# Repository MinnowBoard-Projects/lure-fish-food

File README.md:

# Fish Food Lure for MinnowBoard SBC.

**Fish Food Lure** is a breadboard adapter for the MinnowBoard MAX / Turbot single boards computers (because you feed bread to fish).   
This lure enables fast prototyping on a breadboard, connects to the MinnowBoard using a ribbon cable.      

Lure naming credit goes to John Hawley aka [Warthog9](https://github.com/warthog9) 

You can purchase this lure with *[Netgate](https://store.netgate.com/Lures/FishFood.aspx)*.

> Released under the Creative Commons Attribution 3.0 License     
> https://creativecommons.org/licenses/by/3.0/   
> Designed using DipTrace 3.0

## KiCad version added to this repository. 

> Released under the Creative Commons Attribution 3.0 License     
> https://creativecommons.org/licenses/by/3.0/   
> Designed using KiCad 4.0.7
> Located in this directory: Fish_Food_Lure_KiCad

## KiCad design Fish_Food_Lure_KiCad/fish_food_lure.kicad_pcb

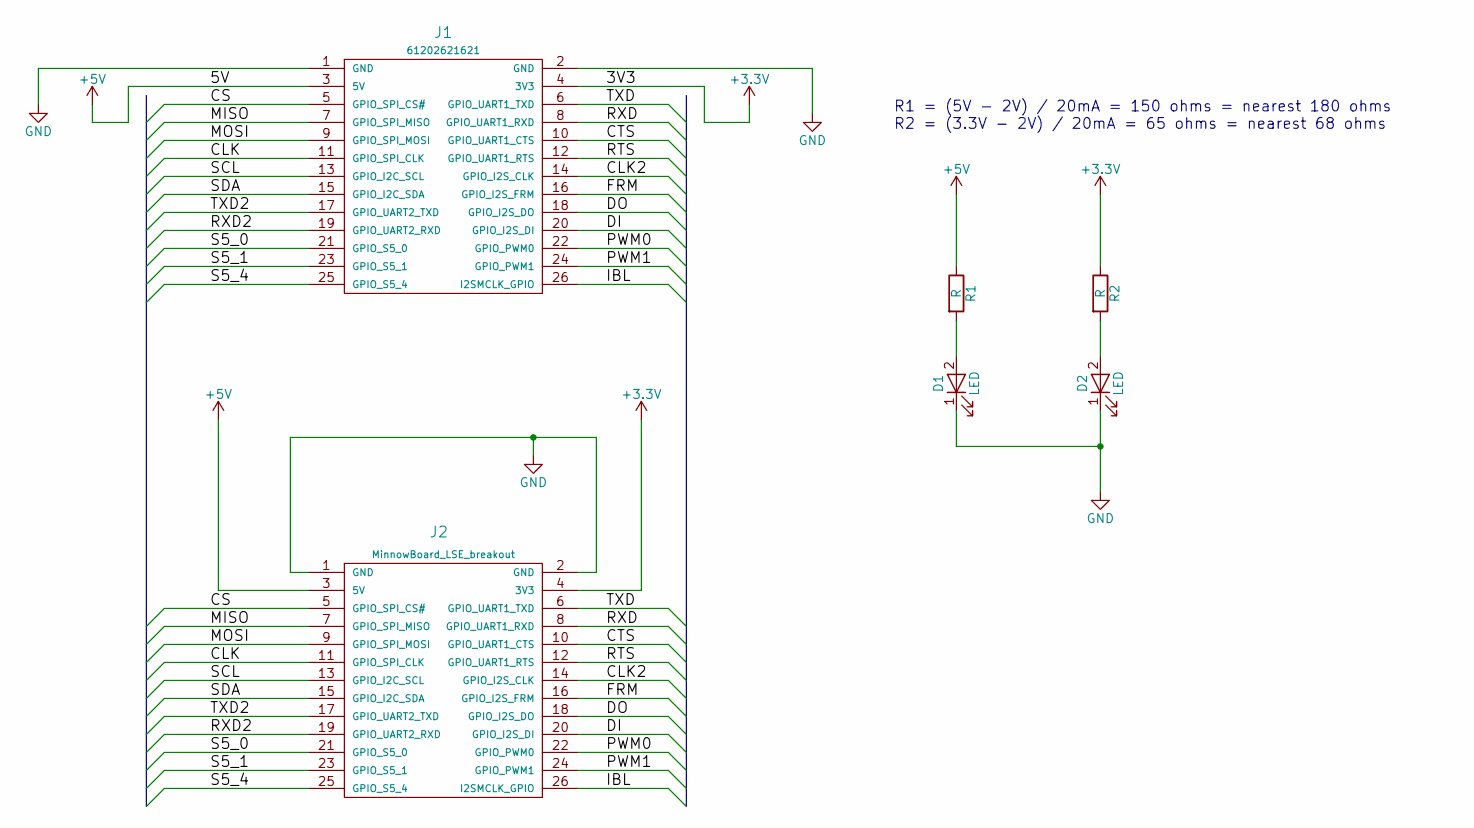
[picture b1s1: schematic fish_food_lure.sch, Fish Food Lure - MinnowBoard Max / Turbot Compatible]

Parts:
D1, D2: LED; LED_0805
J1: 61202621621
J2: MinnowBoard_LSE_breakout; 26_pin_breadboard
R1, R2: R; R_0805

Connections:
+3V3: J1.4 (3V3), J2.4 (3V3), R2.1
+5V: J1.3 (5V), J2.3 (5V), R1.1
/CLK: J1.11 (GPIO_SPI_CLK), J2.11 (GPIO_SPI_CLK)
/CLK2: J1.14 (GPIO_I2S_CLK), J2.14 (GPIO_I2S_CLK)
/CS: J1.5 (GPIO_SPI_CS#), J2.5 (GPIO_SPI_CS#)
/CTS: J1.10 (GPIO_UART1_CTS), J2.10 (GPIO_UART1_CTS)
/DI: J1.20 (GPIO_I2S_DI), J2.20 (GPIO_I2S_DI)
/DO: J1.18 (GPIO_I2S_DO), J2.18 (GPIO_I2S_DO)
/FRM: J1.16 (GPIO_I2S_FRM), J2.16 (GPIO_I2S_FRM)
/IBL: J1.26 (I2SMCLK_GPIO), J2.26 (I2SMCLK_GPIO)
/MISO: J1.7 (GPIO_SPI_MISO), J2.7 (GPIO_SPI_MISO)
/MOSI: J1.9 (GPIO_SPI_MOSI), J2.9 (GPIO_SPI_MOSI)
/PWM0: J1.22 (GPIO_PWM0), J2.22 (GPIO_PWM0)
/PWM1: J1.24 (GPIO_PWM1), J2.24 (GPIO_PWM1)
/RTS: J1.12 (GPIO_UART1_RTS), J2.12 (GPIO_UART1_RTS)
/RXD: J1.8 (GPIO_UART1_RXD), J2.8 (GPIO_UART1_RXD)
/RXD2: J1.19 (GPIO_UART2_RXD), J2.19 (GPIO_UART2_RXD)
/S5_0: J1.21 (GPIO_S5_0), J2.21 (GPIO_S5_0)
/S5_1: J1.23 (GPIO_S5_1), J2.23 (GPIO_S5_1)
/S5_4: J1.25 (GPIO_S5_4), J2.25 (GPIO_S5_4)
/SCL: J1.13 (GPIO_I2C_SCL), J2.13 (GPIO_I2C_SCL)
/SDA: J1.15 (GPIO_I2C_SDA), J2.15 (GPIO_I2C_SDA)
/TXD: J1.6 (GPIO_UART1_TXD), J2.6 (GPIO_UART1_TXD)
/TXD2: J1.17 (GPIO_UART2_TXD), J2.17 (GPIO_UART2_TXD)
GND: D1.1 (K), D2.1 (K), J1.1 (GND), J1.2 (GND), J2.1 (GND), J2.2 (GND)
unnamed: D1.2 (A), R1.2
unnamed: D2.2 (A), R2.2

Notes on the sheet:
R1 = (5V - 2V) / 20mA = 150 ohms = nearest 180 ohms R2 = (3.3V - 2V) / 20mA = 65 ohms = nearest 68 ohms

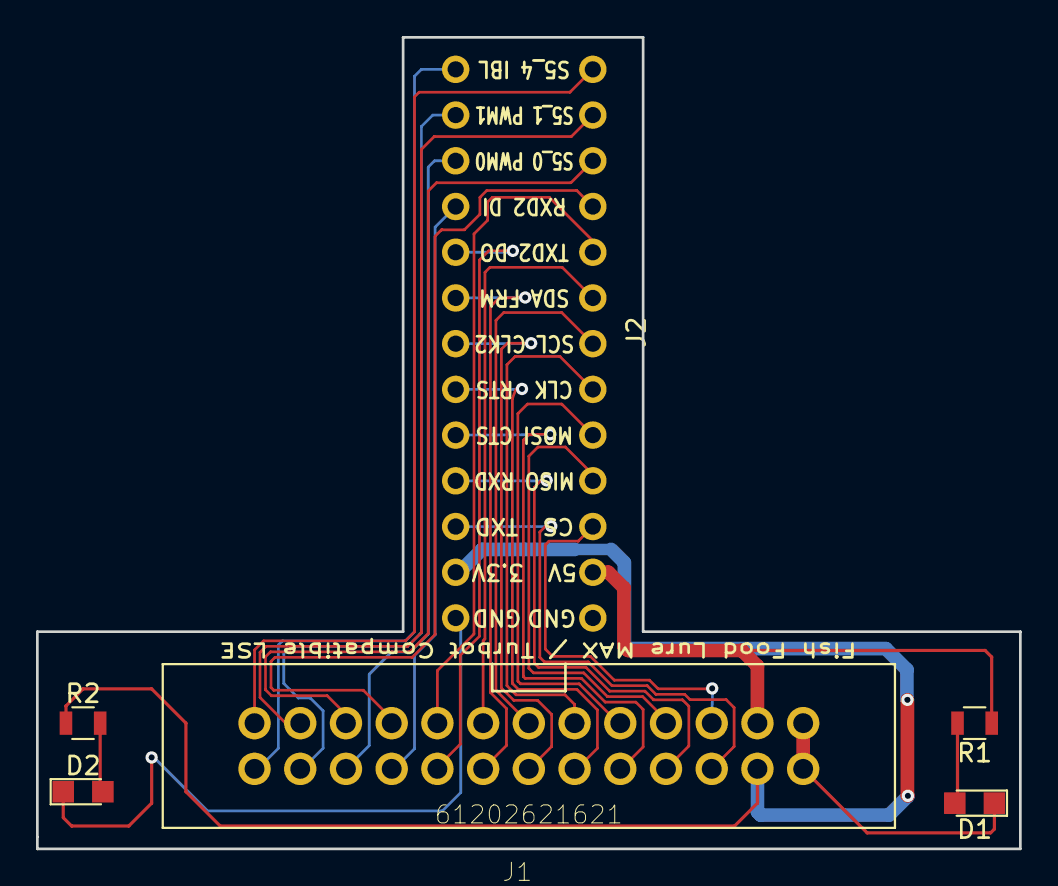
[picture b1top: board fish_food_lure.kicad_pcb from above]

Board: 2 copper layers, 54.6 x 45.1 mm, 6 parts (0 on the bottom side), 27 nets.

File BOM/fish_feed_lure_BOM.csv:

RefDes,Value,Name,Manufacturer part,Manufacturer,Quantity,Link26pin,929834-01-13,13 position pin strip,929834-01-13,3M Electronic Solutions Division,2,http://www.mouser.com/ProductDetail/3M/929834-01-13/?qs=FRjC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D1,Green LED,DIODE_0805,SML-LXT0805GW-TRLumex,,1,http://www.mouser.com/Search/ProductDetail.aspx?R=SML-LXT080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D2,Red LED,DIODE_0805,SML-LXT0805IW-TR,Lumex,1,http://www.mouser.com/Search/ProductDetail.aspx?R=SML-LXT080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R1,180 ohms,RES_0805 ERJ-6GEYJ181V,ERJ-6GEYJ181V,Panasonic,1,http://www.mouser.com/Search/ProductDetail.aspx?R=ERJ-6GEYJ1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R2,68 ohms,RES_0805  SG73S2ATTD680J,SG73S2ATTD680J,KOA Speer,1,http://www.mouser.com/Search/ProductDetail.aspx?R=SG73S2ATTD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ShroudedHeader,61202621621,Shrouded MAX / Turbot Compatible LSE,61202621621,Wurth Electronics,1,http://www.mouser.com/Search/ProductDetail.aspx?R=6120262162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

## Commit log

2016-06-23 Initial commit
    Initial commit of the Fish Food Lure.
2016-06-23 Moved schematic
    Moved schematic
2016-06-24 BOM update
    Updated BOM with current replacement for the 13 pin header.
2016-06-24 Update
    Added license in which this project has been released.
2016-08-19 Silkscreen Fix
    Silkscreen fix and gerber files refresh.
2017-06-10 Typo fix on schematic file and PDF schematic
    Typo fix on schematic file and PDF schematic, changed from Fish Feed
    Lure to Fish Food Lure.
2020-08-19 Added KiCad port
    Added the KiCad port of the Fish Food Lure
2020-08-19 Create placeholder
